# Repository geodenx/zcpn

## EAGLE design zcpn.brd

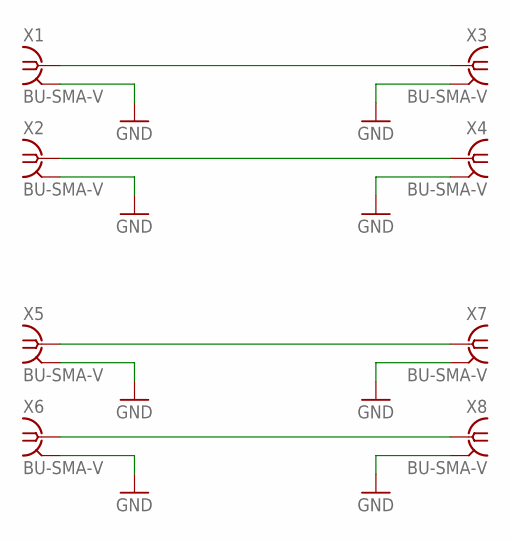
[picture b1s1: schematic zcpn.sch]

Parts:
X1, X2, X3, X4, X5, X6, X7, X8: BU-SMA-V

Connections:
GND: X1.2, X1.3 (2), X1.4 (2), X1.5 (2), X2.2, X2.3 (2), X2.4 (2), X2.5 (2), X3.2, X3.3 (2), X3.4 (2), X3.5 (2), X4.2, X4.3 (2), X4.4 (2), X4.5 (2), X5.2, X5.3 (2), X5.4 (2), X5.5 (2), X6.2, X6.3 (2), X6.4 (2), X6.5 (2), X7.2, X7.3 (2), X7.4 (2), X7.5 (2), X8.2, X8.3 (2), X8.4 (2), X8.5 (2)
SMA0_N: X2.1, X4.1
SMA0_P: X1.1, X3.1
SMA1_N: X6.1, X8.1
SMA1_P: X5.1, X7.1

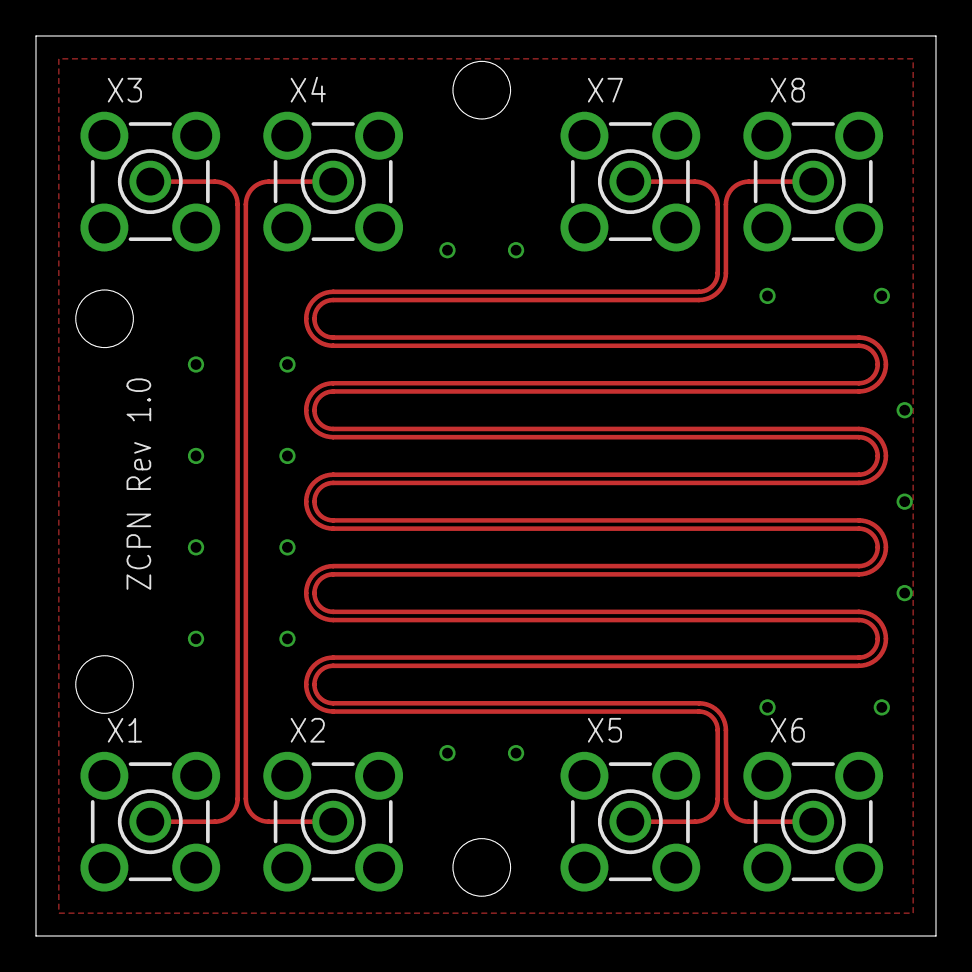
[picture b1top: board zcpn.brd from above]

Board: 2 copper layers, 50.0 x 50.0 mm, 8 parts (0 on the bottom side), 5 nets.

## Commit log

2014-11-25 Asked Elecrow for fabrication
